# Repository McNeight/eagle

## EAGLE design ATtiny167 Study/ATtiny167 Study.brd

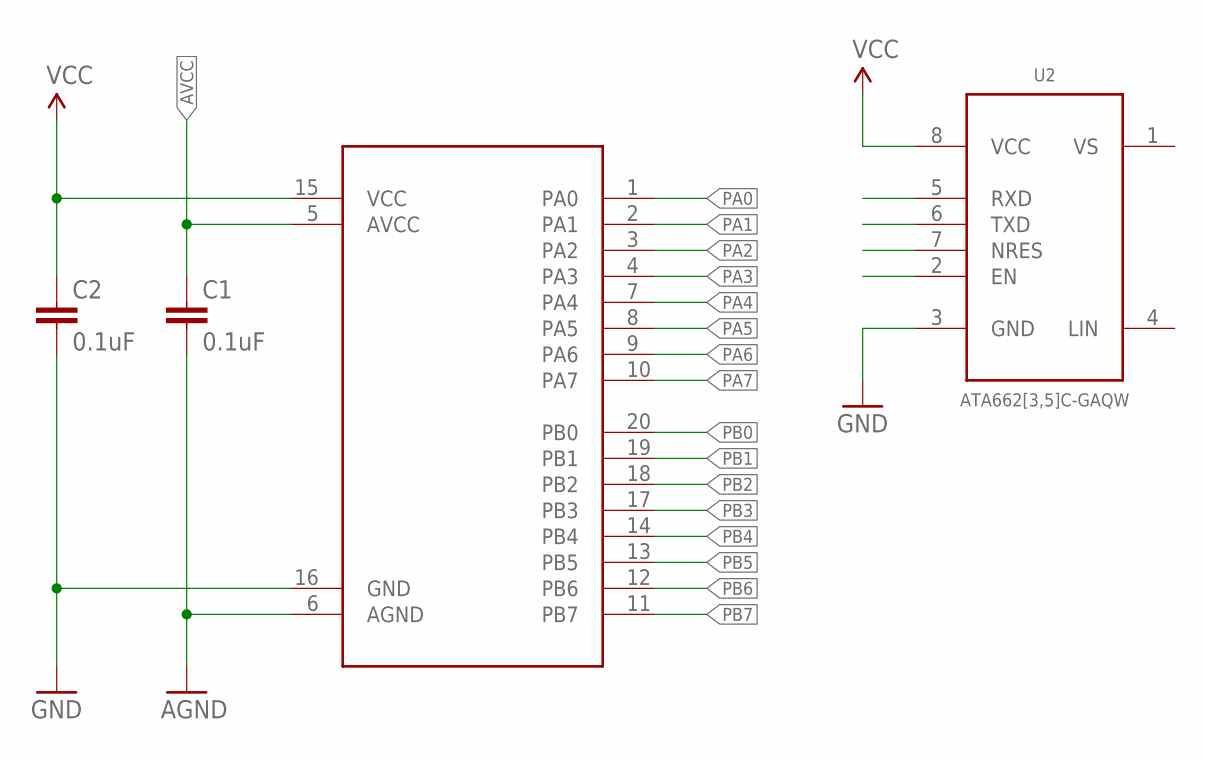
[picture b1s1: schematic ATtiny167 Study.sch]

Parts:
C1, C2: 0.1uF; 0603-CAP
U1: ATTINY87-SU; 20S2
U2: ATA662[3,5]C-GAQW; 8S1

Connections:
AGND: C1.2, U1.6 (AGND)
AVCC: C1.1, U1.5 (AVCC)
GND: C2.2, U1.16 (GND), U2.3 (GND)
PA0: U1.1 (PA0)
PA1: U1.2 (PA1)
PA2: U1.3 (PA2)
PA3: U1.4 (PA3)
PA4: U1.7 (PA4)
PA5: U1.8 (PA5)
PA6: U1.9 (PA6)
PA7: U1.10 (PA7)
PB0: U1.20 (PB0)
PB1: U1.19 (PB1)
PB2: U1.18 (PB2)
PB3: U1.17 (PB3)
PB4: U1.14 (PB4)
PB5: U1.13 (PB5)
PB6: U1.12 (PB6)
PB7: U1.11 (PB7)
VCC: C2.1, U1.15 (VCC), U2.8 (VCC)
VS: U2.1 (VS)

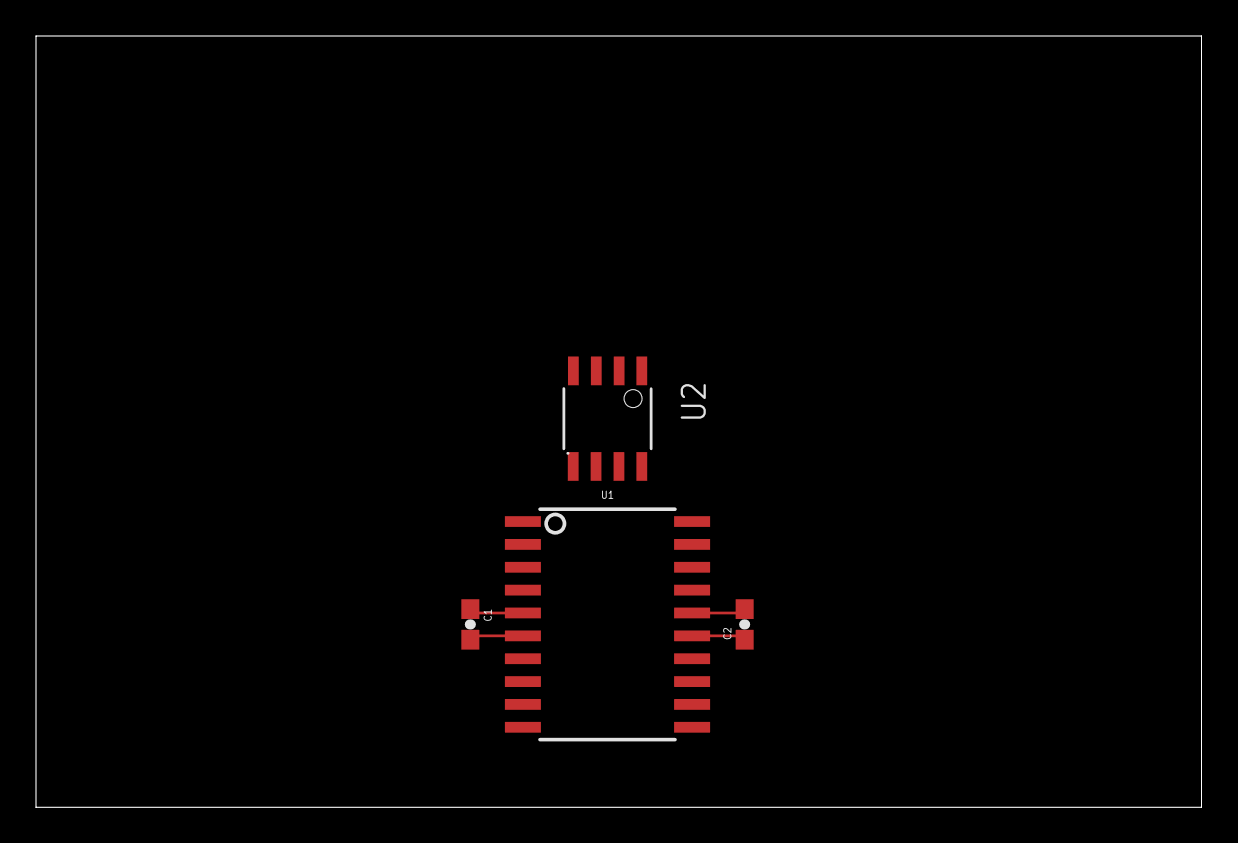
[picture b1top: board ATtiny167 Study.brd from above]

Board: 2 copper layers, 64.8 x 42.9 mm, 4 parts (0 on the bottom side), 4 nets.

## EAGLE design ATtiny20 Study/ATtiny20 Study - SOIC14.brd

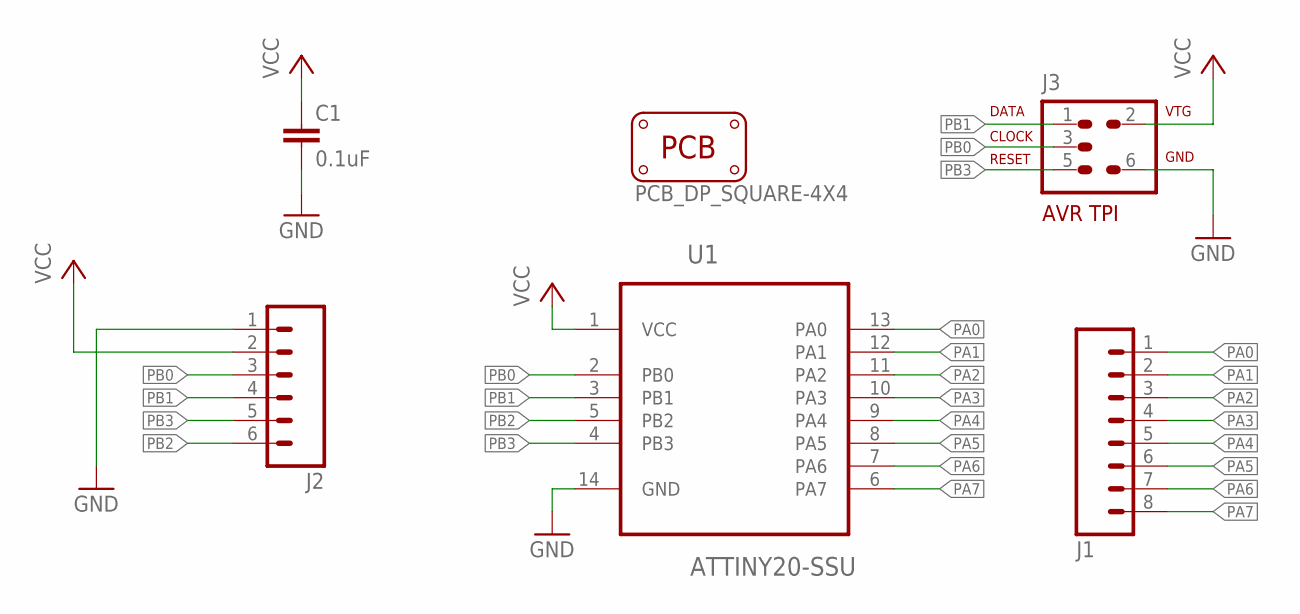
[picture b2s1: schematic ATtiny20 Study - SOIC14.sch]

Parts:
C1: 0.1uF; 0805
J1: M08NO_SILK_FEMALE_PTH; 1X08_NO_SILK
J2: M06NO_SILK_FEMALE_PTH; 1X06_NO_SILK
J3: AVR-TPIVERT; AVR-ISP-6
PCB1: PCB_DP_SQUARE-4X4; DP4040_V1
U1: ATTINY20-SSU; 14S1

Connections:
GND: C1.2, J2.1, J3.6, U1.14 (GND)
PA0: J1.1, U1.13 (PA0)
PA1: J1.2, U1.12 (PA1)
PA2: J1.3, U1.11 (PA2)
PA3: J1.4, U1.10 (PA3)
PA4: J1.5, U1.9 (PA4)
PA5: J1.6, U1.8 (PA5)
PA6: J1.7, U1.7 (PA6)
PA7: J1.8, U1.6 (PA7)
PB0: J2.3, J3.3, U1.2 (PB0)
PB1: J2.4, J3.1, U1.3 (PB1)
PB2: J2.6, U1.5 (PB2)
PB3: J2.5, J3.5, U1.4 (PB3)
VCC: C1.1, J2.2, J3.2, U1.1 (VCC)

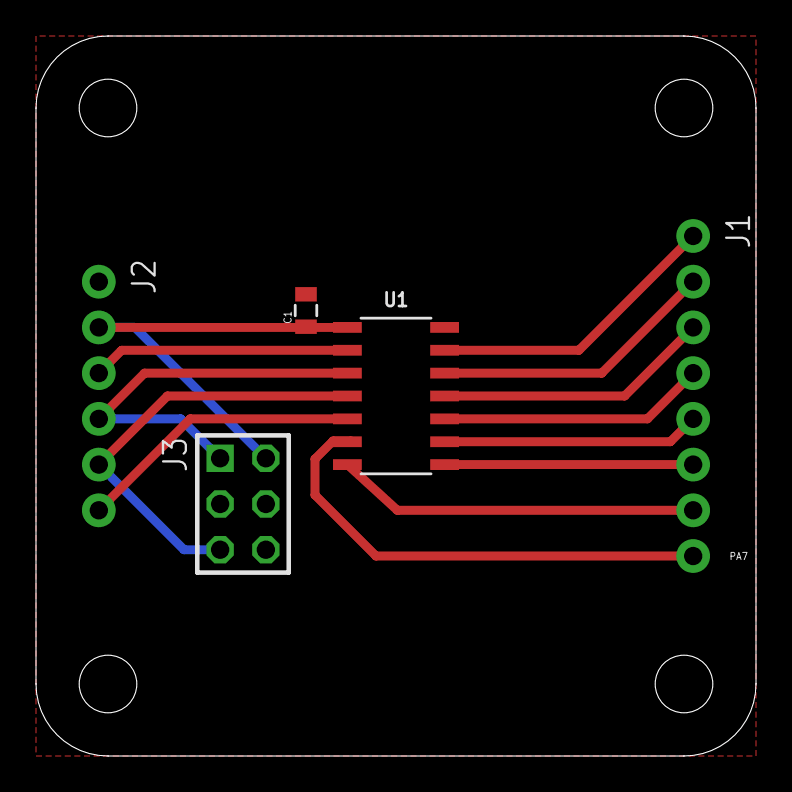
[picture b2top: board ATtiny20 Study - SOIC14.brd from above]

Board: 2 copper layers, 40.0 x 40.0 mm, 6 parts (0 on the bottom side), 14 nets.

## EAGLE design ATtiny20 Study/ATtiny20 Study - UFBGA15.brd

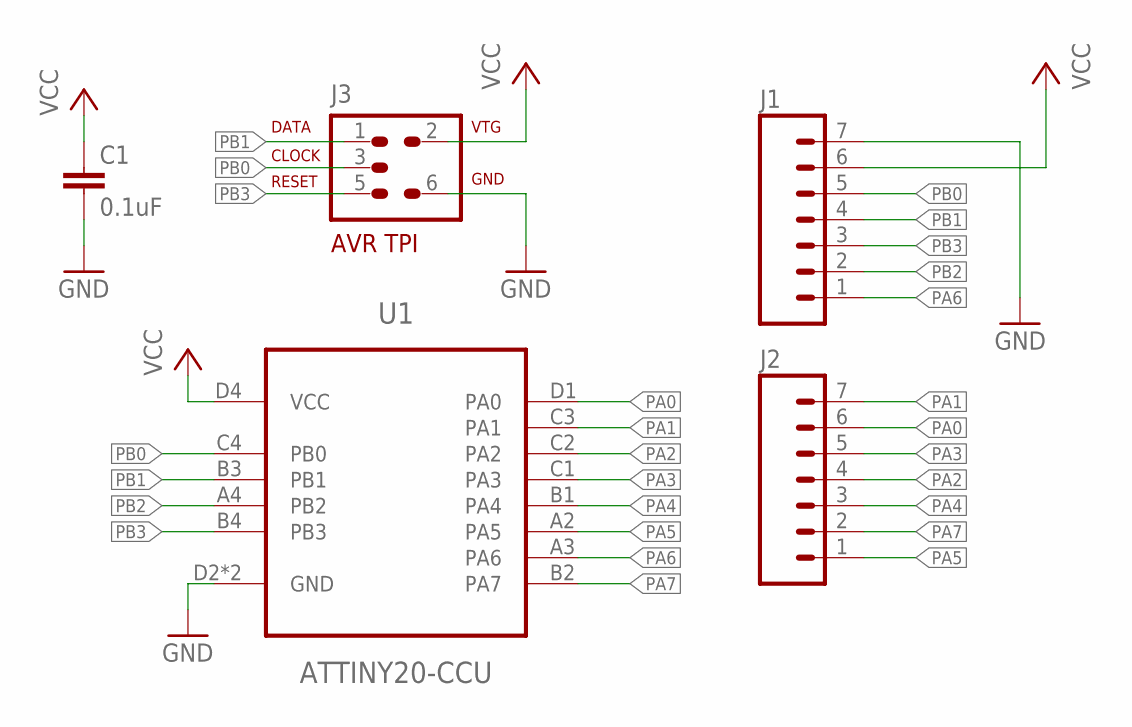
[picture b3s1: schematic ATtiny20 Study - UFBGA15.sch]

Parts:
C1: 0.1uF; 0402-CAP
J1, J2: M07; 1X07
J3: AVR-TPIVERT; AVR-ISP-6
U1: ATTINY20-CCU; 15CC1

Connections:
GND: C1.2, J1.7, J3.6, U1.D2 (GND), U1.D3 (GND)
PA0: J2.6, U1.D1 (PA0)
PA1: J2.7, U1.C3 (PA1)
PA2: J2.4, U1.C2 (PA2)
PA3: J2.5, U1.C1 (PA3)
PA4: J2.3, U1.B1 (PA4)
PA5: J2.1, U1.A2 (PA5)
PA6: J1.1, U1.A3 (PA6)
PA7: J2.2, U1.B2 (PA7)
PB0: J1.5, J3.3, U1.C4 (PB0)
PB1: J1.4, J3.1, U1.B3 (PB1)
PB2: J1.2, U1.A4 (PB2)
PB3: J1.3, J3.5, U1.B4 (PB3)
VCC: C1.1, J1.6, J3.2, U1.D4 (VCC)

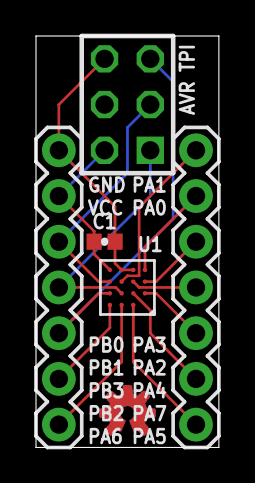
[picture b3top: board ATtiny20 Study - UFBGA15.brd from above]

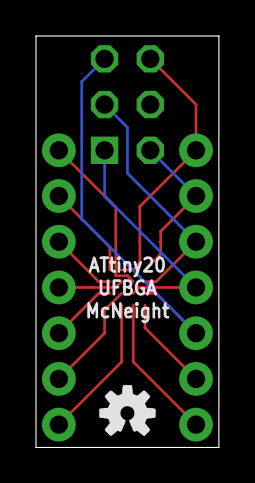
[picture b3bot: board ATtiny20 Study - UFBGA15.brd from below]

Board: 2 copper layers, 10.2 x 22.9 mm, 8 parts (2 on the bottom side), 14 nets.

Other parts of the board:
U$1, U$2: OSHW-LOGO-S_COPPER
U$3: OSHW-LOGO-S

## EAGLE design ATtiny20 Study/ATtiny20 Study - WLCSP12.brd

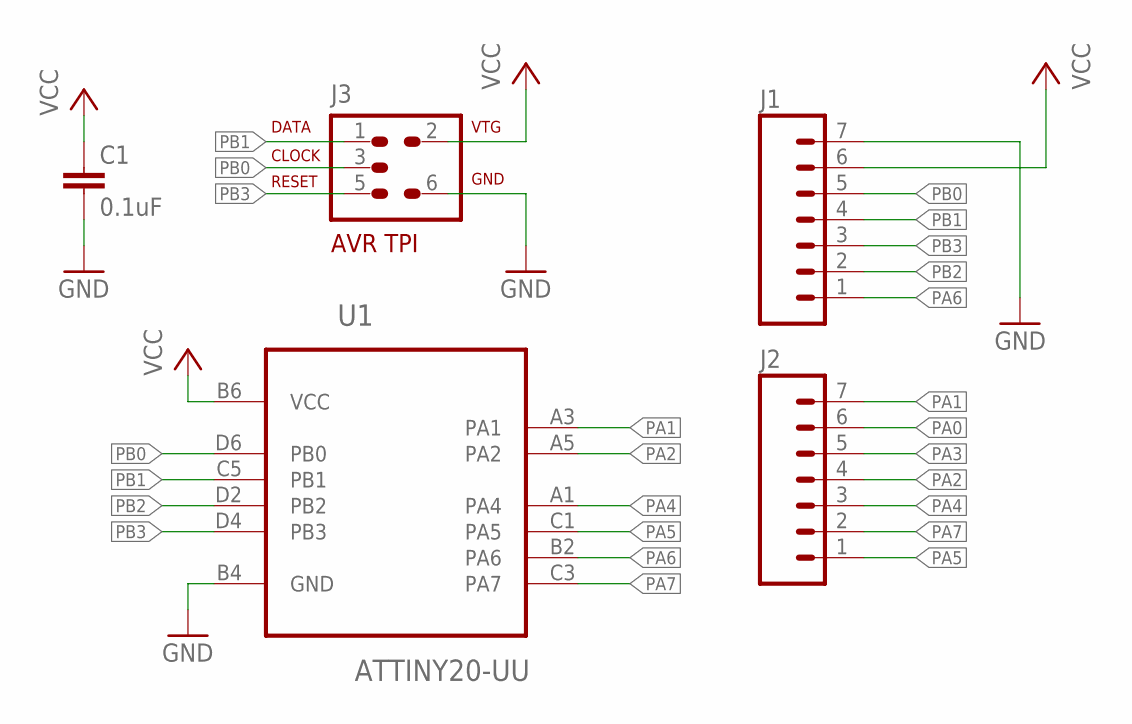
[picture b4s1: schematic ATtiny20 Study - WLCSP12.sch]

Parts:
C1: 0.1uF; 0402-CAP
J1, J2: M07; 1X07
J3: AVR-TPIVERT; AVR-ISP-6
U1: ATTINY20-UU; 12U-1

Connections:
GND: C1.2, J1.7, J3.6, U1.B4 (GND)
PA0: J2.6
PA1: J2.7, U1.A3 (PA1)
PA2: J2.4, U1.A5 (PA2)
PA3: J2.5
PA4: J2.3, U1.A1 (PA4)
PA5: J2.1, U1.C1 (PA5)
PA6: J1.1, U1.B2 (PA6)
PA7: J2.2, U1.C3 (PA7)
PB0: J1.5, J3.3, U1.D6 (PB0)
PB1: J1.4, J3.1, U1.C5 (PB1)
PB2: J1.2, U1.D2 (PB2)
PB3: J1.3, J3.5, U1.D4 (PB3)
VCC: C1.1, J1.6, J3.2, U1.B6 (VCC)

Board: 2 copper layers, 7 parts (1 on the bottom side), 12 nets, no tracks yet.

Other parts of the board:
U$1, U$2: OSHW-LOGO-S_COPPER

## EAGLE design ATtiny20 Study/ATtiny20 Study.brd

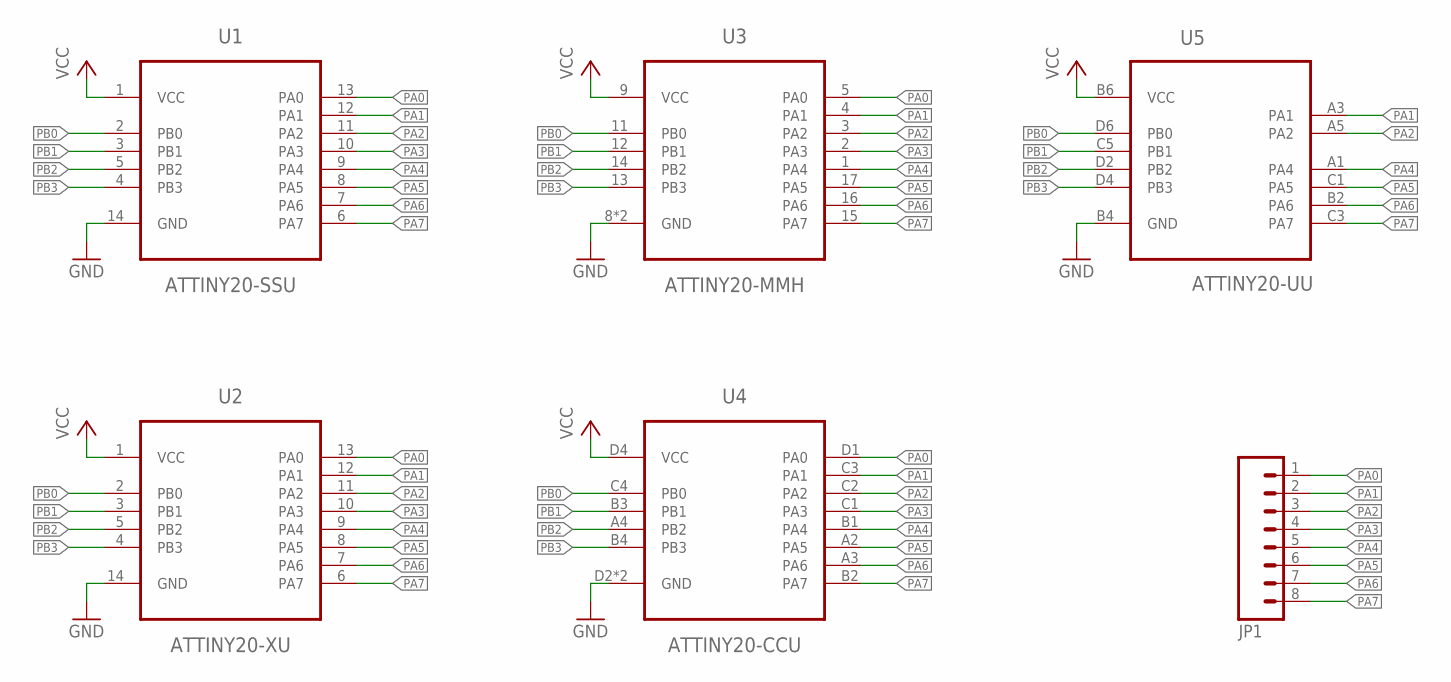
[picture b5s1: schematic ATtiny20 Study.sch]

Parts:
JP1: M08LOCK_NO_SILK; 1X08_LOCK_NO_SILK
U1: ATTINY20-SSU; 14S1
U2: ATTINY20-XU; 14X
U3: ATTINY20-MMH; 20M2
U4: ATTINY20-CCU; 15CC1
U5: ATTINY20-UU; 12U-1

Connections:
GND: U1.14 (GND), U2.14 (GND), U3.8 (GND), U3.PAD (GND), U4.D2 (GND), U4.D3 (GND), U5.B4 (GND)
PA0: JP1.1, U1.13 (PA0), U2.13 (PA0), U3.5 (PA0), U4.D1 (PA0)
PA1: JP1.2, U1.12 (PA1), U2.12 (PA1), U3.4 (PA1), U4.C3 (PA1), U5.A3 (PA1)
PA2: JP1.3, U1.11 (PA2), U2.11 (PA2), U3.3 (PA2), U4.C2 (PA2), U5.A5 (PA2)
PA3: JP1.4, U1.10 (PA3), U2.10 (PA3), U3.2 (PA3), U4.C1 (PA3)
PA4: JP1.5, U1.9 (PA4), U2.9 (PA4), U3.1 (PA4), U4.B1 (PA4), U5.A1 (PA4)
PA5: JP1.6, U1.8 (PA5), U2.8 (PA5), U3.17 (PA5), U4.A2 (PA5), U5.C1 (PA5)
PA6: JP1.7, U1.7 (PA6), U2.7 (PA6), U3.16 (PA6), U4.A3 (PA6), U5.B2 (PA6)
PA7: JP1.8, U1.6 (PA7), U2.6 (PA7), U3.15 (PA7), U4.B2 (PA7), U5.C3 (PA7)
PB0: U1.2 (PB0), U2.2 (PB0), U3.11 (PB0), U4.C4 (PB0), U5.D6 (PB0)
PB1: U1.3 (PB1), U2.3 (PB1), U3.12 (PB1), U4.B3 (PB1), U5.C5 (PB1)
PB2: U1.5 (PB2), U2.5 (PB2), U3.14 (PB2), U4.A4 (PB2), U5.D2 (PB2)
PB3: U1.4 (PB3), U2.4 (PB3), U3.13 (PB3), U4.B4 (PB3), U5.D4 (PB3)
VCC: U1.1 (VCC), U2.1 (VCC), U3.9 (VCC), U4.D4 (VCC), U5.B6 (VCC)

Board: 4 copper layers, 6 parts (0 on the bottom side), 14 nets, no tracks yet.

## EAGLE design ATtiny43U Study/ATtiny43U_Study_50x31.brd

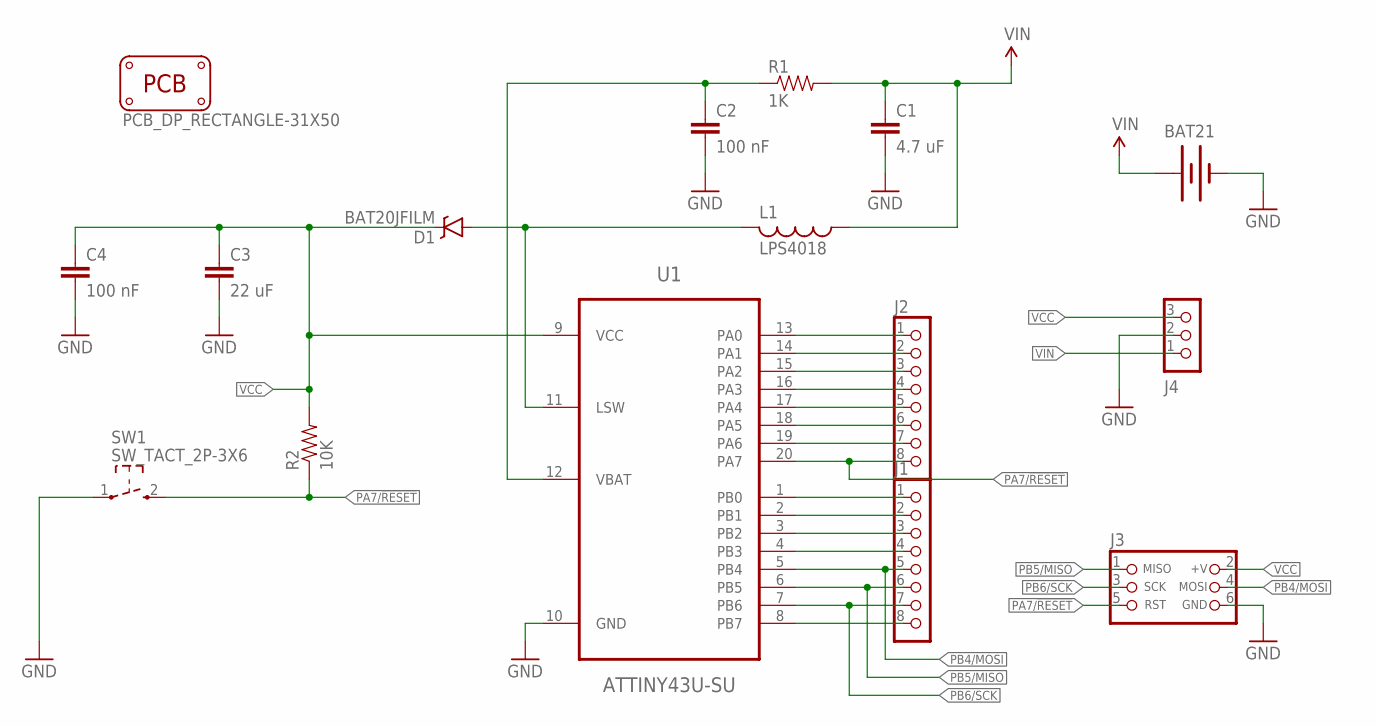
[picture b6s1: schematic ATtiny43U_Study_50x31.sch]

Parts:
BAT21: BATTERYAAA; BATTERY-AAA
C1: 4.7 uF; 0805; PARTNO GRM219R60J475KE19
C2, C4: 100 nF; 0603-CAP
C3: 22 uF; 0805; PARTNO GRM21BR60J226ME39
D1: BAT20JFILM; SOD-323; PARTNO PMEG2005EJ
J1, J2: CON_HEADER_1X08-PTH; M1X8
J3: CON_HEADER_PRG_AVR_ICSP-PTH; HEADER_PRG_2X03
J4: CON_HEADER_1X03-PTH; M1X3
L1: LPS4018; PARTNO LPS4018-153MRB
PCB2: PCB_DP_RECTANGLE-31X50; DP5031_V1
R1: 1K; 0603-RES
R2: 10K; 0603-RES
SW1: SW_TACT_2P-3X6; SW_TACT_3X6
U1: ATTINY43U-SU; 20S2

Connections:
GND: BAT21.GND@1 (-), C1.2, C2.2, C3.2, C4.2, J3.6 (GND), J4.2, SW1.1, U1.10 (GND)
LSW: D1.A, L1.P$2 (2), U1.11 (LSW)
PA0: J2.1, U1.13 (PA0)
PA1: J2.2, U1.14 (PA1)
PA2: J2.3, U1.15 (PA2)
PA3: J2.4, U1.16 (PA3)
PA4: J2.5, U1.17 (PA4)
PA5: J2.6, U1.18 (PA5)
PA6: J2.7, U1.19 (PA6)
PA7/!RESET: J2.8, J3.5 (RST), R2.1, SW1.2 (3), U1.20 (PA7)
PB0: J1.1, U1.1 (PB0)
PB1: J1.2, U1.2 (PB1)
PB2: J1.3, U1.3 (PB2)
PB3: J1.4, U1.4 (PB3)
PB4/MOSI: J1.5, J3.4 (MOSI), U1.5 (PB4)
PB5/MISO: J1.6, J3.1 (MISO), U1.6 (PB5)
PB6/SCK: J1.7, J3.3 (SCK), U1.7 (PB6)
PB7: J1.8, U1.8 (PB7)
VBAT: C2.1, R1.1, U1.12 (VBAT)
VCC: C3.1, C4.1, D1.C, J3.2 (+V), J4.3, R2.2, U1.9 (VCC)
VIN: BAT21.PWR@1 (+), C1.1, J4.1, L1.P$1 (1), R1.2

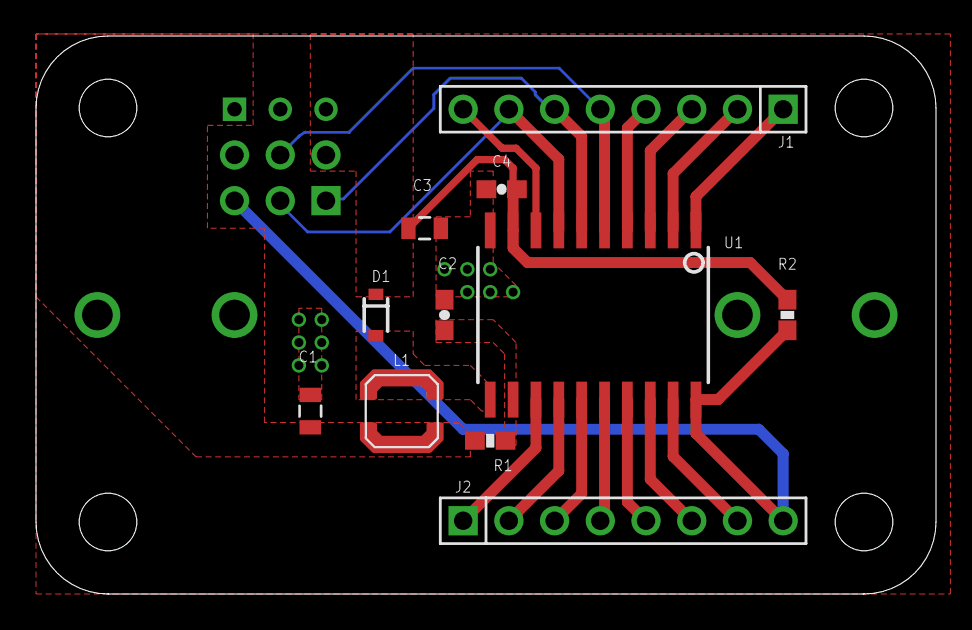
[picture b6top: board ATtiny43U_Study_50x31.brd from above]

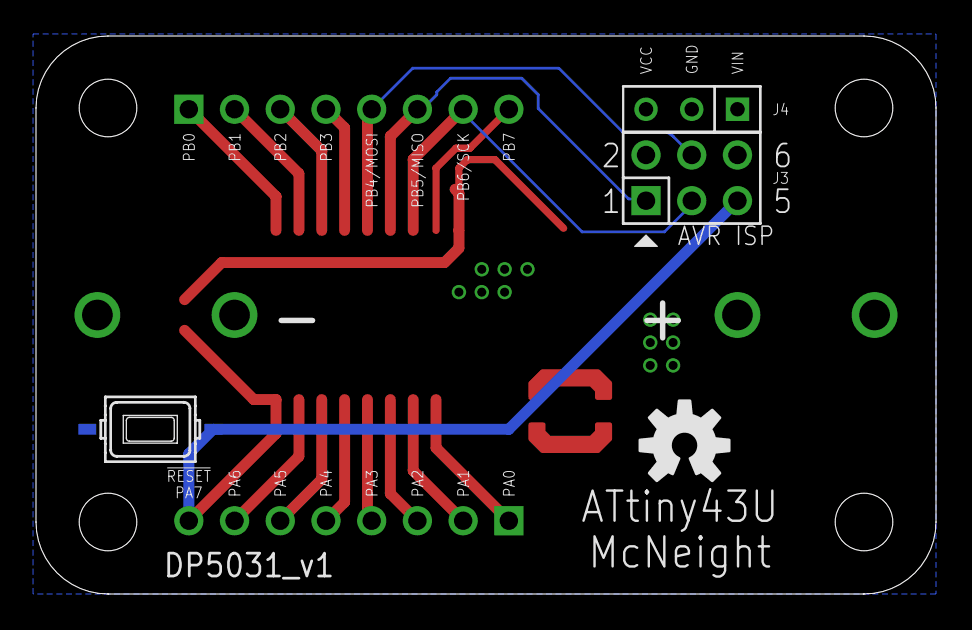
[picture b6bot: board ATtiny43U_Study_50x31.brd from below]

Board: 2 copper layers, 50.0 x 31.0 mm, 17 parts (5 on the bottom side), 21 nets.

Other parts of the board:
U$1: OSHW-LOGO-M

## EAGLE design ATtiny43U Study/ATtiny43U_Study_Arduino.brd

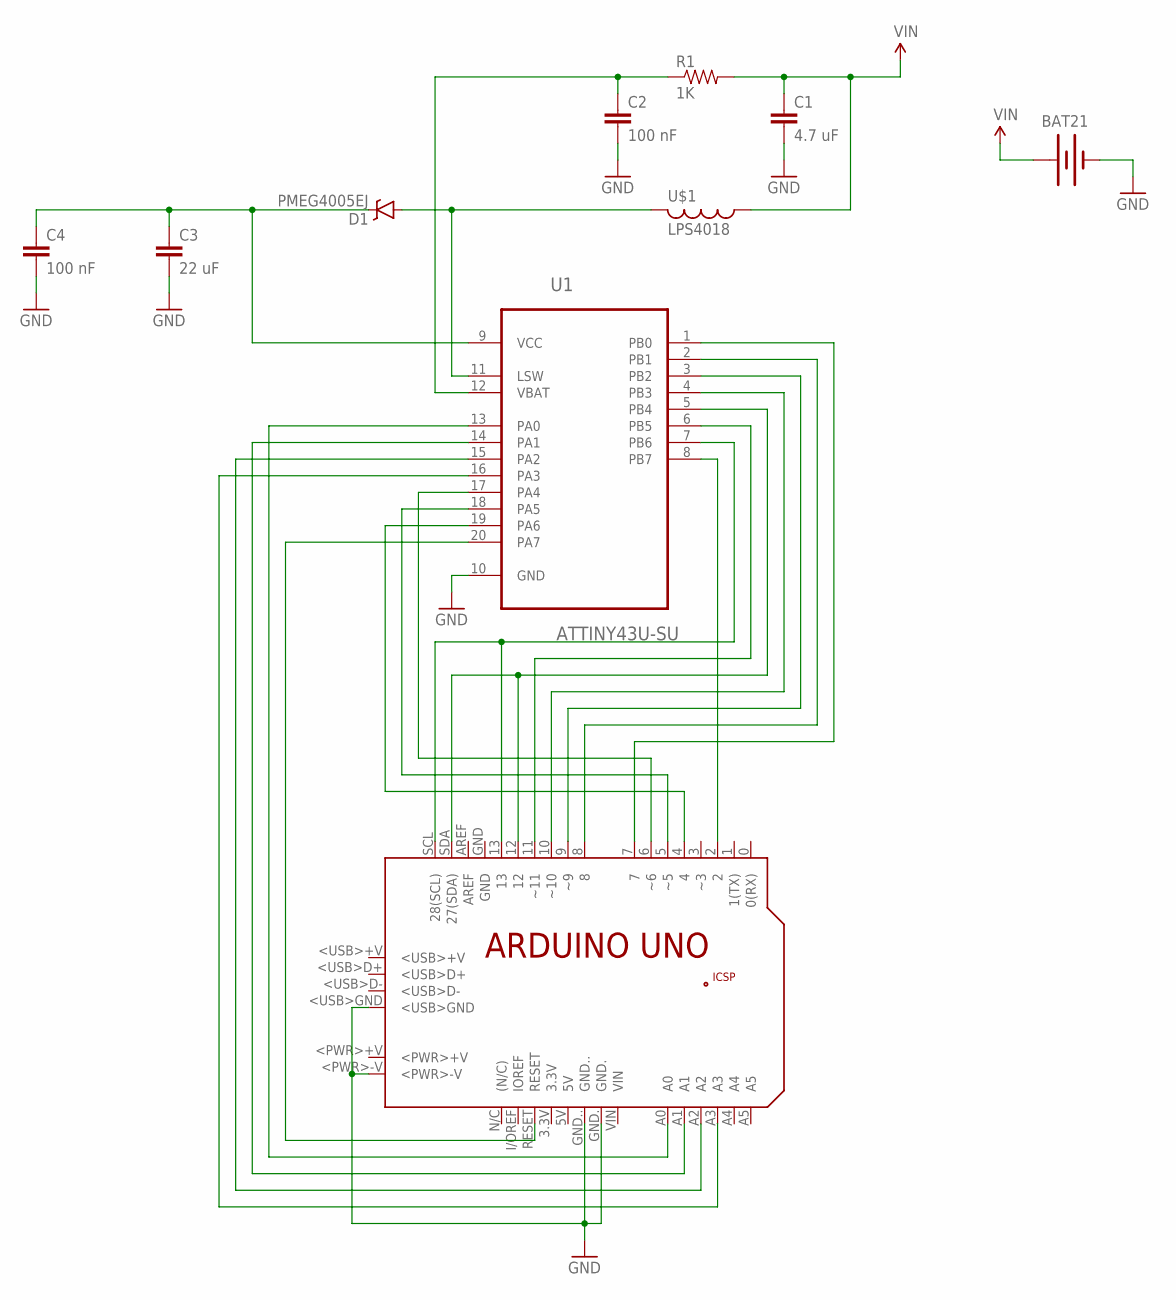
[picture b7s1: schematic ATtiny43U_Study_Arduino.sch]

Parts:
BAT21: BATTERYAAA; BATTERY-AAA
C1: 4.7 uF; 0805; PARTNO GRM219R60J475KE19
C2, C4: 100 nF; 0603-CAP
C3: 22 uF; 0805; PARTNO GRM21BR60J226ME39
D1: PMEG4005EJ; SOD-323; PARTNO PMEG2005EJ
PCB1: ARDUINO_UNO
R1: 1K; 0603-RES
U1: ATTINY43U-SU; SOIC127P1032X265-20N
U$1: LPS4018; PARTNO LPS4018-153MRB

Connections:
3.3V: PCB1.3.3V
5V: PCB1.5V
+5V: PCB1.+5V
<PWR>+V: PCB1.<PWR>+V
<USB>+V: PCB1.<USB>+V
GND: BAT21.GND@1 (-), C1.2, C2.2, C3.2, C4.2, PCB1.<PWR>-V, PCB1.<USB>GND, PCB1.GND, PCB1.GND., PCB1.GND.., U1.10 (GND)
GND_: PCB1.GND_
LSW: D1.A, U1.11 (LSW), U$1.P$2 (2)
unnamed: PCB1.A0, U1.13 (PA0)
unnamed: PCB1.A1, U1.14 (PA1)
unnamed: PCB1.A2, U1.15 (PA2)
unnamed: PCB1.A3, U1.16 (PA3)
unnamed: PCB1.RESET, U1.20 (PA7)
unnamed: PCB1.12, PCB1.SDA (27(SDA)), U1.5 (PB4)
unnamed: PCB1.13, PCB1.SCL (28(SCL)), U1.7 (PB6)
unnamed: PCB1.2, U1.8 (PB7)
unnamed: PCB1.10 (~10), U1.4 (PB3)
unnamed: PCB1.11 (~11), U1.6 (PB5)
unnamed: PCB1.9 (~9), U1.3 (PB2)
unnamed: PCB1.8, U1.2 (PB1)
unnamed: PCB1.7, U1.1 (PB0)
unnamed: PCB1.6 (~6), U1.17 (PA4)
unnamed: PCB1.5 (~5), U1.18 (PA5)
unnamed: PCB1.4, U1.19 (PA6)
VBAT: C2.1, R1.1, U1.12 (VBAT)
VCC: C3.1, C4.1, D1.C, U1.9 (VCC)
VIN: BAT21.PWR@1 (+), C1.1, PCB1.VIN, R1.2, U$1.P$1 (1)

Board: 2 copper layers, 10 parts (0 on the bottom side), 21 nets, no tracks yet.

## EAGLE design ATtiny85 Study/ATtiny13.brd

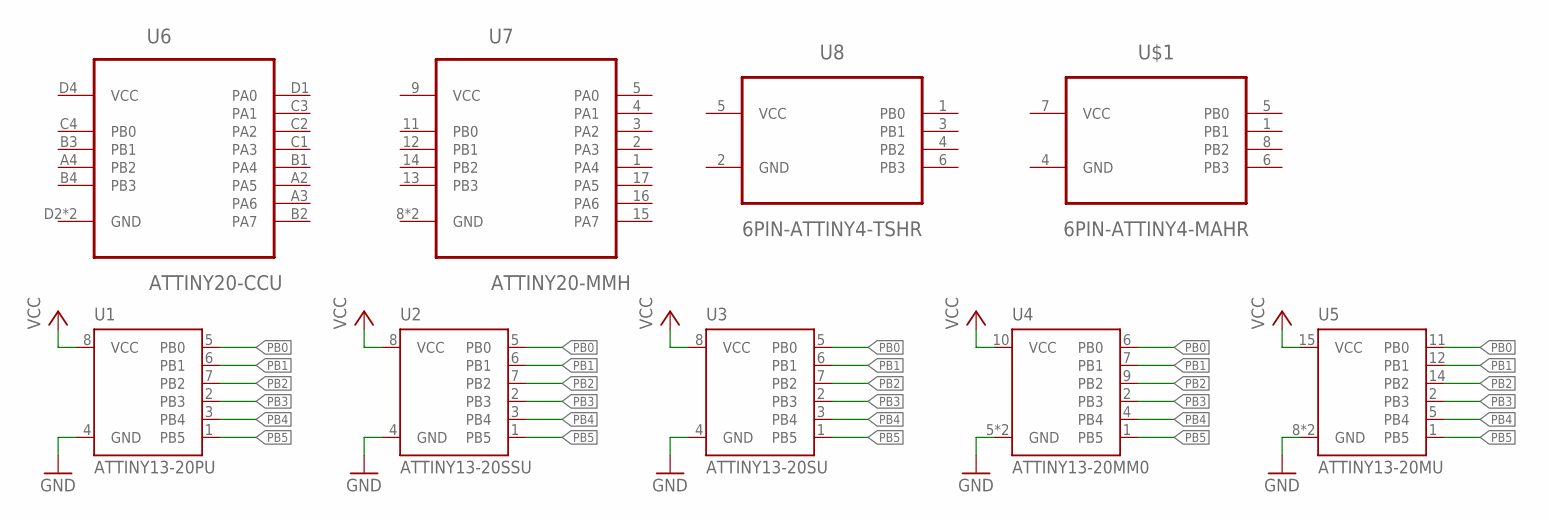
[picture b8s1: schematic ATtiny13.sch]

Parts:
U1: ATTINY13-20PU; 8P3
U2: ATTINY13-20SSU; 8S1
U3: ATTINY13-20SU; 8S2
U4: ATTINY13-20MM0; 10M1
U5: ATTINY13-20MU; 20M1
U6: ATTINY20-CCU; 15CC1
U7: ATTINY20-MMH; 20M2
U8: 6PIN-ATTINY4-TSHR; 6ST1
U$1: 6PIN-ATTINY4-MAHR; 8MA4

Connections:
GND: U1.4 (GND), U2.4 (GND), U3.4 (GND), U4.5 (GND), U4.11 (GND), U5.8 (GND), U5.21 (GND)
PB0: U1.5 (PB0), U2.5 (PB0), U3.5 (PB0), U4.6 (PB0), U5.11 (PB0)
PB1: U1.6 (PB1), U2.6 (PB1), U3.6 (PB1), U4.7 (PB1), U5.12 (PB1)
PB2: U1.7 (PB2), U2.7 (PB2), U3.7 (PB2), U4.9 (PB2), U5.14 (PB2)
PB3: U1.2 (PB3), U2.2 (PB3), U3.2 (PB3), U4.2 (PB3), U5.2 (PB3)
PB4: U1.3 (PB4), U2.3 (PB4), U3.3 (PB4), U4.4 (PB4), U5.5 (PB4)
PB5: U1.1 (PB5), U2.1 (PB5), U3.1 (PB5), U4.1 (PB5), U5.1 (PB5)
VCC: U1.8 (VCC), U2.8 (VCC), U3.8 (VCC), U4.10 (VCC), U5.15 (VCC), U6.D4 (VCC), U7.9 (VCC), U8.5 (VCC), U$1.7 (VCC)

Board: 2 copper layers, 9 parts (0 on the bottom side), 8 nets, no tracks yet.

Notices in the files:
parts and their libraries:
SparkFun-Capacitors: Licensing: Creative Commons ShareAlike 4.0 International - https://creativecommons.org/licenses/by-sa/4.0
